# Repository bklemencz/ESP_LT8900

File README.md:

ESP8266 to LT8900 series 2.4G Gateway

MILIGHT remote control command parsing and sending json on MQTT.
If data is not MILIGHT protocol it sends on MQTT as raw buffer.
MQTT command subscribe to send data on 2.4G radio.

Updated HW with more sensors:
https://github.com/bklemencz/RF_24G_Gateway

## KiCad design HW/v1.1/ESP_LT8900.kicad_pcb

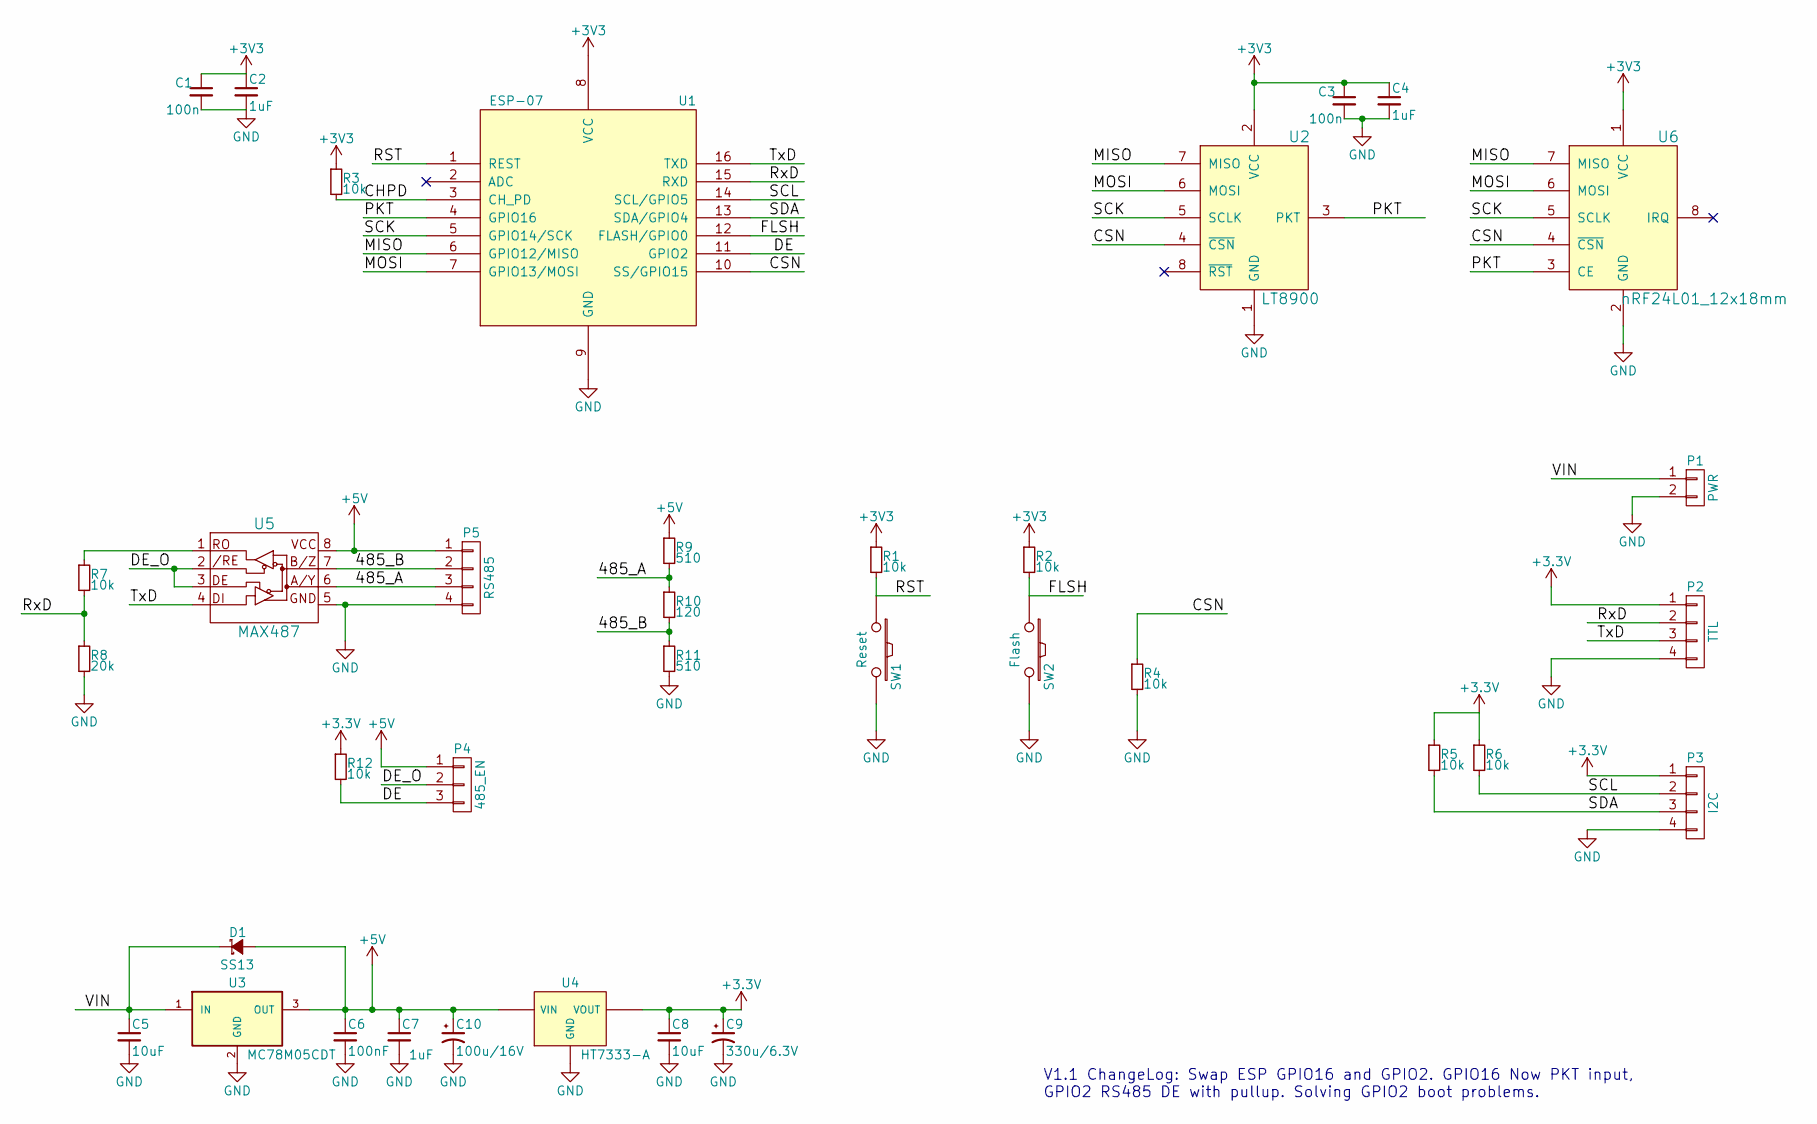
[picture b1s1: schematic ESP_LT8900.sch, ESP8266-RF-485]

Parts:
C1, C3: 100n; C_0805
C2, C4: 1uF; C_0805
C5, C8: 10uF; C_1206
C6: 100nF; C_0805
C7: 1uF; C_1206
C9: 330u/6.3V; CP_Elec_6.3x7.7
C10: 100u/16V; CP_Elec_6.3x5.3
D1: SS13; D_SMA_Standard
P1: PWR; JST_B2B-XH-A
P2: TTL; Pin_Header_Straight_1x04_Pitch2.54mm
P3: I2C; Pin_Header_Straight_1x04_Pitch2.54mm
P4: 485_EN; Pin_Header_Straight_1x03_Pitch2.54mm
P5: RS485; Pin_Header_Straight_1x04_Pitch2.54mm
R1, R2, R3, R4, R5, R6, R7, R12: 10k; R_0805
R8: 20k; R_0805
R9, R11: 510; R_0805
R10: 120; R_0805
SW1: Reset; SW_SPST_FSMSM
SW2: Flash; SW_SPST_FSMSM
U1: ESP-07; ESP-07v2
U2: LT8900; LT8900_2.54mmPitch_SMD_20x20
U3: MC78M05CDT; TO-252-2Lead
U4: HT7333-A; SOT89-3_Housing
U5: MAX487; SOIC-8_3.9x4.9mm_Pitch1.27mm
U6: nRF24L01_12x18mm; NRF24L01_12x18mm

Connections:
+5V: C6.1, C7.1, C10.1, D1.2 (A), P4.1, P5.1, R9.1, U3.3 (OUT), U4.2 (VIN), U5.8 (VCC)
/485_A: P5.3, R9.2, R10.1, U5.6 (A/Y)
/485_B: P5.2, R10.2, R11.1, U5.7 (B/Z)
/CHPD: R3.2, U1.3 (CH_PD)
/CSN: R4.1, U1.10 (SS/GPIO15), U2.4 (~CSN), U6.4 (~CSN)
/DE: P4.3, R12.2, U1.11 (GPIO2)
/DE_O: P4.2, U5.2 (/RE), U5.3 (DE)
/FLSH: R2.2, SW2.1, U1.12 (FLASH/GPIO0)
/MISO: U1.6 (GPIO12/MISO), U2.7 (MISO), U6.7 (MISO)
/MOSI: U1.7 (GPIO13/MOSI), U2.6 (MOSI), U6.6 (MOSI)
/PKT: U1.4 (GPIO16), U2.3 (PKT), U6.3 (CE)
/RST: R1.2, SW1.1, U1.1 (REST)
/RxD: P2.2, R7.2, R8.1, U1.15 (RXD)
/SCK: U1.5 (GPIO14/SCK), U2.5 (SCLK), U6.5 (SCLK)
/SCL: P3.2, R6.2, U1.14 (SCL/GPIO5)
/SDA: P3.3, R5.2, U1.13 (SDA/GPIO4)
/TxD: P2.3, U1.16 (TXD), U5.4 (DI)
/VIN: C5.1, D1.1 (K), P1.1, U3.1 (IN)
GND: C1.2, C2.2, C3.2, C4.2, C5.2, C6.2, C7.2, C8.2, C9.2, C10.2, P1.2, P2.4, P3.4, P5.4, R4.2, R8.2, R11.2, SW1.2, SW2.2, U1.9 (GND), U2.1 (GND), U3.2 (GND), U4.1 (GND), U5.5 (GND), U6.2 (GND); also elsewhere on the board
unnamed: R7.1, U5.1 (RO)

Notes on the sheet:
V1.1 ChangeLog: Swap ESP GPIO16 and GPIO2. GPIO16 Now PKT input, GPIO2 RS485 DE with pullup. Solving GPIO2 boot problems.

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
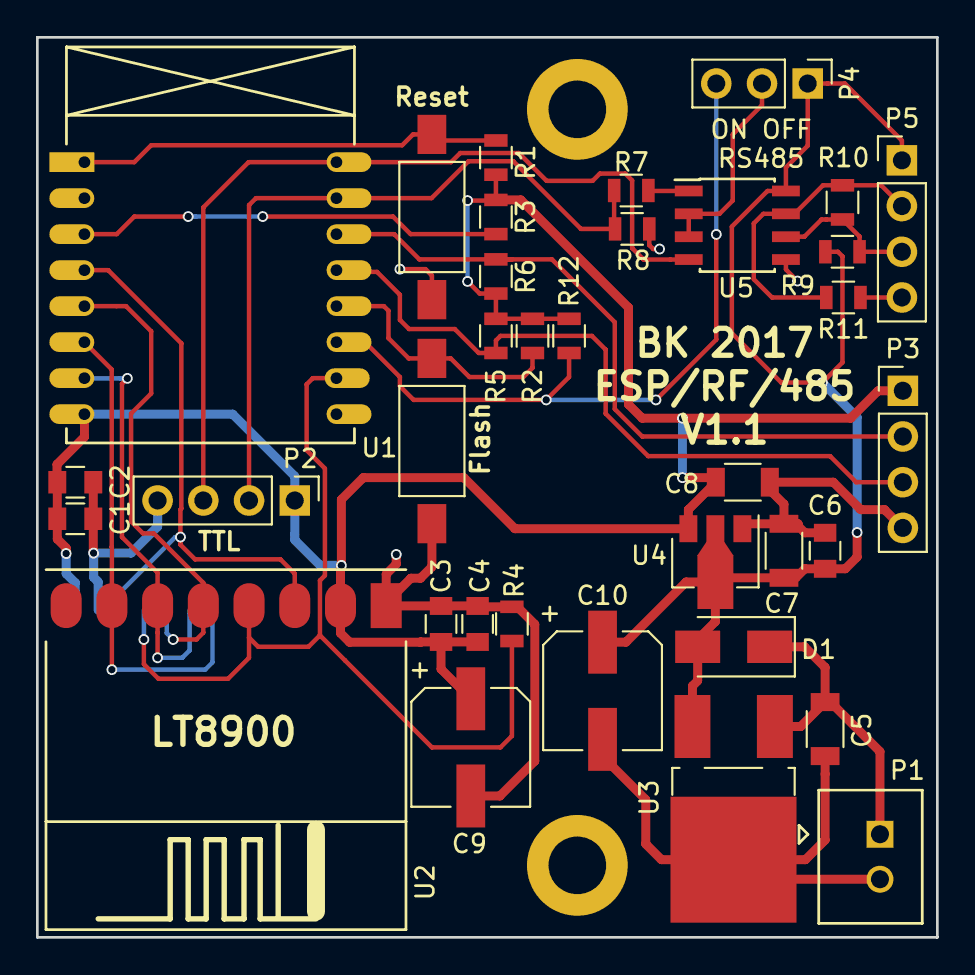
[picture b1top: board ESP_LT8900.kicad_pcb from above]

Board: 2 copper layers, 50.0 x 50.0 mm, 38 parts (1 on the bottom side), 21 nets.

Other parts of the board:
M1, M2: MountingHole_3.2mm_M3_DIN965_Pad

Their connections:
GND: M1.1, M2.1; also elsewhere on the board

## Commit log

2017-04-03 :confetti_ball: Added .gitattributes & .gitignore files
2017-04-03 Initial
2017-05-30 HW &SW Folder Update
2017-05-30 PDF Folder
2017-06-12 SW Upd
2017-06-12 LT8900 Update
    Use without PKT pin
2017-06-14 LT8900 Update
2017-06-14 HW v1.0 folder
2017-06-15 HW v1.1
    Swap ESP GPIO16 and GPIO2. Pullup on GPIO2.
2017-07-04 Baro Sensor Upd
2020-12-31 Json and transmit
